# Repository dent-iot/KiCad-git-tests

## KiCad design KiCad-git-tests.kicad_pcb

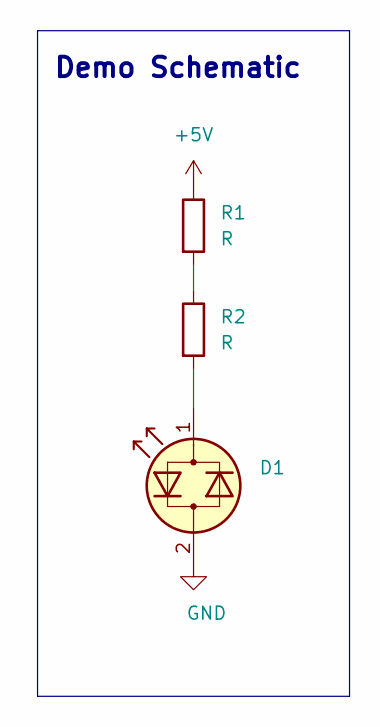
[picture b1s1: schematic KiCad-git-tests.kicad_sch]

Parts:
D1: LED_Dual_Bidirectional; LED_1812_4532Metric_Pad1.30x3.40mm_HandSolder
R1, R2: R; R_0612_1632Metric

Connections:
+5V: R1.1
GND: D1.2 (AK)
unnamed: D1.1 (KA), R2.2
unnamed: R1.2, R2.1

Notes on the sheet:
Demo Schematic

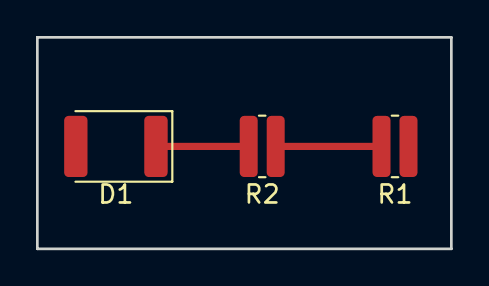
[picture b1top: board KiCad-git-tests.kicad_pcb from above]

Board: 2 copper layers, 23.0 x 11.8 mm, 3 parts (0 on the bottom side), 2 nets.
